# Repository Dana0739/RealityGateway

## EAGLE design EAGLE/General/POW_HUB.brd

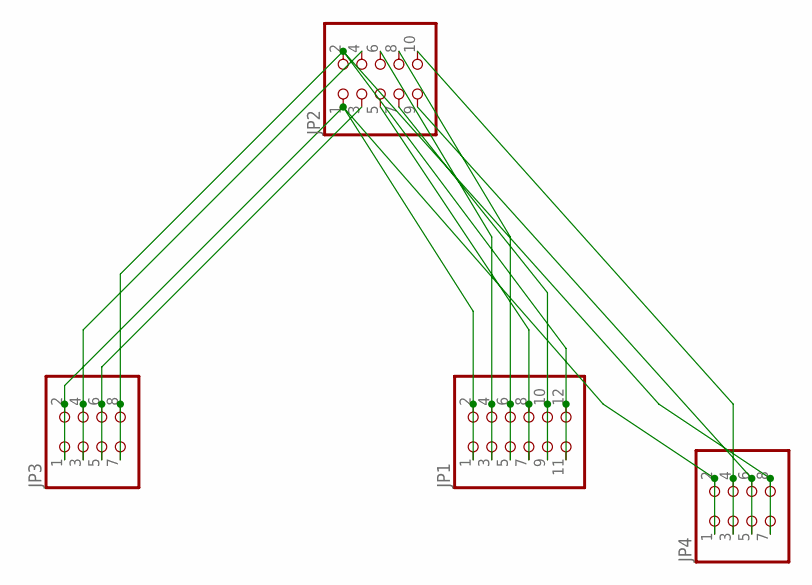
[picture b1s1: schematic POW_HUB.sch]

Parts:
JP1: PINHD-2X6; 2X06
JP2: PINHD-2X5; 2X05
JP3, JP4: PINHD-2X4; 2X04

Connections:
unnamed: JP1.1, JP1.2, JP2.1, JP3.1, JP3.2, JP4.1, JP4.2
unnamed: JP1.11, JP1.12, JP2.2, JP3.7, JP3.8, JP4.7, JP4.8
unnamed: JP2.3, JP3.5, JP3.6
unnamed: JP2.4, JP3.3, JP3.4
unnamed: JP1.3, JP1.4, JP2.6
unnamed: JP1.5, JP1.6, JP2.8
unnamed: JP1.7, JP1.8, JP2.5
unnamed: JP1.9, JP1.10, JP2.7
unnamed: JP2.10, JP4.3, JP4.4
unnamed: JP2.9, JP4.5, JP4.6

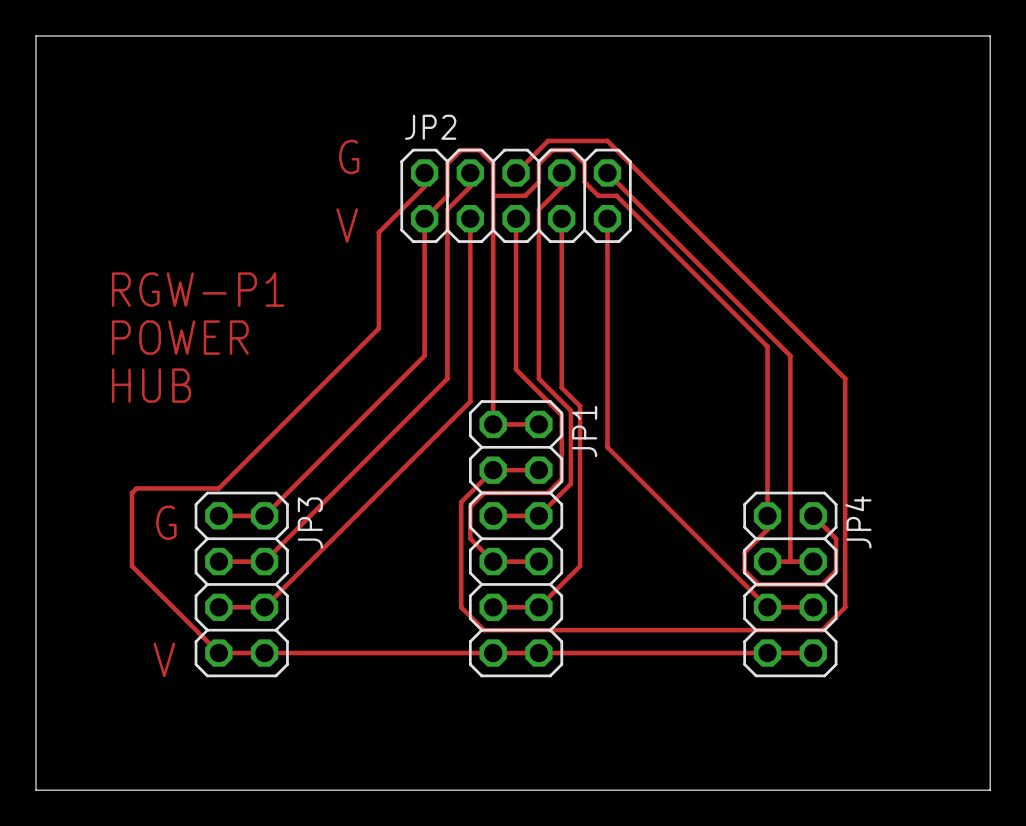
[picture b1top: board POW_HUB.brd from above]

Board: 2 copper layers, 53.0 x 41.9 mm, 4 parts (0 on the bottom side), 10 nets.

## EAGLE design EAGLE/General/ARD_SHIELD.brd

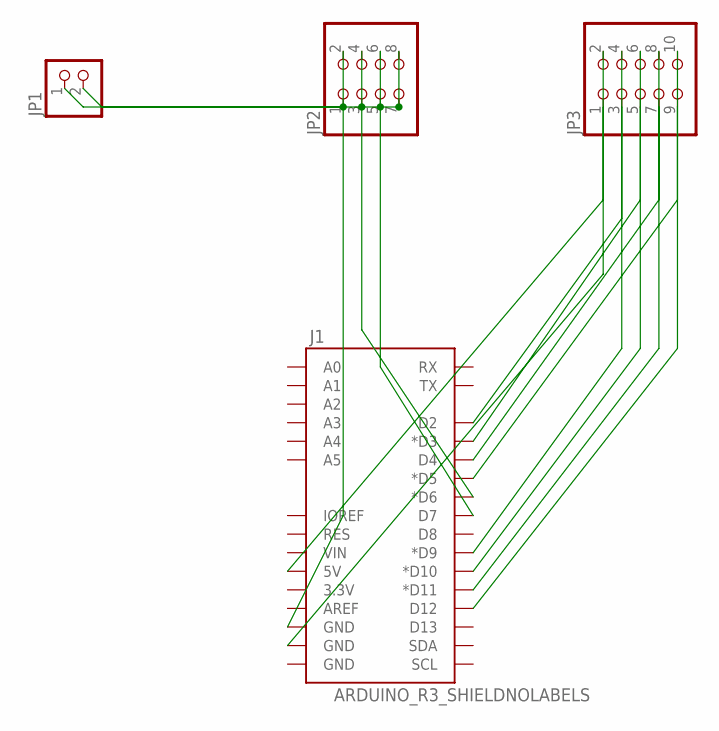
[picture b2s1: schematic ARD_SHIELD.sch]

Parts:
J1: ARDUINO_R3_SHIELDNOLABELS; UNO_R3_SHIELD_NOLABELS
JP1: PINHD-1X2; 1X02
JP2: PINHD-2X4; 2X04
JP3: PINHD-2X5; 2X05

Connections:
unnamed: J1.GND@2 (GND), JP1.2, JP2.1, JP2.2
unnamed: J1.D6 (*D6), JP2.3, JP2.4
unnamed: J1.D7, JP2.5, JP2.6
unnamed: JP1.1, JP2.7, JP2.8
unnamed: J1.5V, JP3.1
unnamed: J1.GND@1 (GND), JP3.2
unnamed: J1.D9 (*D9), JP3.3
unnamed: J1.D10 (*D10), JP3.5
unnamed: J1.D11 (*D11), JP3.7
unnamed: J1.D12, JP3.9
unnamed: J1.D2, JP3.4
unnamed: J1.D3 (*D3), JP3.6
unnamed: J1.D4, JP3.8
unnamed: J1.D5 (*D5), JP3.10

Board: 2 copper layers, 4 parts (0 on the bottom side), 14 nets, no tracks yet.

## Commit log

2017-03-24 Create UBUNTU 14-04 INSTALLATION
2017-06-26 Rename Mono-0.1 to Mono-0.1.txt
2018-04-18 Rename blink_and_servo.c to Blink_and_servo.c
2018-06-11 Rename AZIMUTH.ino to Azimuth.ino
2018-07-01 Create Хаюшки!!!)
2019-02-03 КВЕСТ
    7) ну вот и все, теперь только о том, кто мы тебе. мы, люди, которые тебя окружили и мучили сегодня столько часов... мы - твоё семейство. а как ты знаешь (или нет, но мне пофиг, я тут издеваться над 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

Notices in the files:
parts and their libraries:
SparkFun-Boards: Licensing: Creative Commons ShareAlike 4.0 International - https://creativecommons.org/licenses/by-sa/4.0
